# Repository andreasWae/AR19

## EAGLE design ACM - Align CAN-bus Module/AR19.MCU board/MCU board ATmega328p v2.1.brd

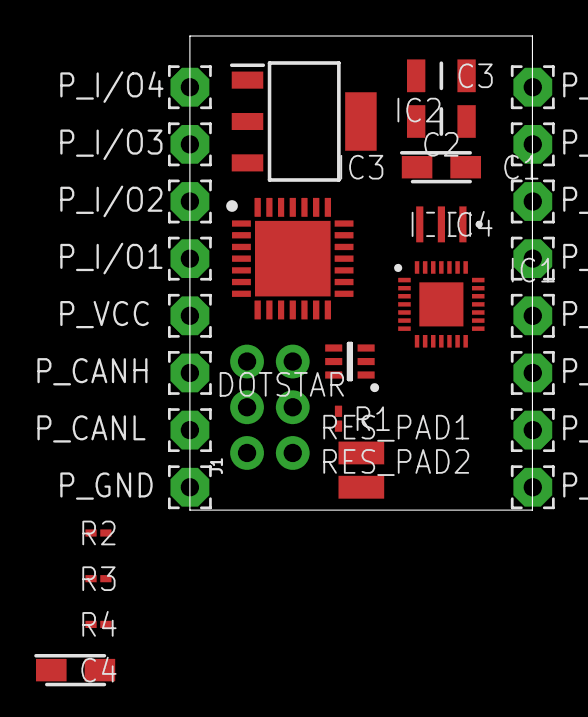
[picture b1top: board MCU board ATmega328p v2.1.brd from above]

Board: 2 copper layers, 19.0 x 26.3 mm, 32 parts (0 on the bottom side), 18 nets, no tracks yet.

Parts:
C1, C4: 10uF; CAPPM3216X180N
C2, C3: 22pF; CAPC3216X229N
DOTSTAR: COM-14608; SON75P200X200X100-6N
IC1: ATMEGA328P-MMH; QFN45P400X400X100-29N
IC2: MIC5239-5.0YS_TR; SOT230P700X170-4N
IC3: MCP25625-E_ML; QFN65P600X600X100-29N
IC4: 16Mhz; CSTCE16M0V13C99R0
J1: AVR_SPI_PROG_3X2NS; 2X3-NS
P_CANH: 2,15/1,0
P_CANL: 2,15/1,0
P_GND: 2,15/1,0
P_I/O1, P_I/O2, P_I/O3, P_I/O4, P_I/O5, P_I/O6, P_I/O7, P_I/O8, P_I/O9, P_I/O10, P_I/O11, P_I/O12: 2,15/1,0
P_VCC: 2,15/1,0
R1: 10K ohm; RESC0603X28N
R2, R3, R4: 500 ohm; RESC0603X28N
RES_PAD1, RES_PAD2: SMD1,27-2,54

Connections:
5V: C1.1, DOTSTAR.4, IC1.3, IC2.3, IC3.3, IC3.19, J1.2, R1.2
CANH: IC3.13, P_CANH.1
CANL: IC3.12, P_CANL.1
GND: C1.2, C4.1, DOTSTAR.3, IC2.2, IC3.22, IC4.2, J1.6, P_GND.1, RES_PAD2.1
MISO: IC1.14, J1.1, R2.2
MISO_MCP: IC3.28, R2.1
MOSI: IC1.13, J1.4, R3.2
MOSI_MCP: IC3.27, R3.1
unnamed: C2.1, IC4.1
unnamed: C3.1, IC4.3
OSC1: C2.2, IC1.5, IC3.21
OSC2: C3.2, IC1.6, IC3.20
RESET_MCU: IC1.25, J1.5, R1.1, RES_PAD1.1
RXCAN: IC3.5, IC3.10
SCK: IC1.15, J1.3, R4.2
SCK_MCP: IC3.26, R4.1
TXCAN: IC3.4, IC3.16
VCC: C4.2, IC2.1, P_VCC.1

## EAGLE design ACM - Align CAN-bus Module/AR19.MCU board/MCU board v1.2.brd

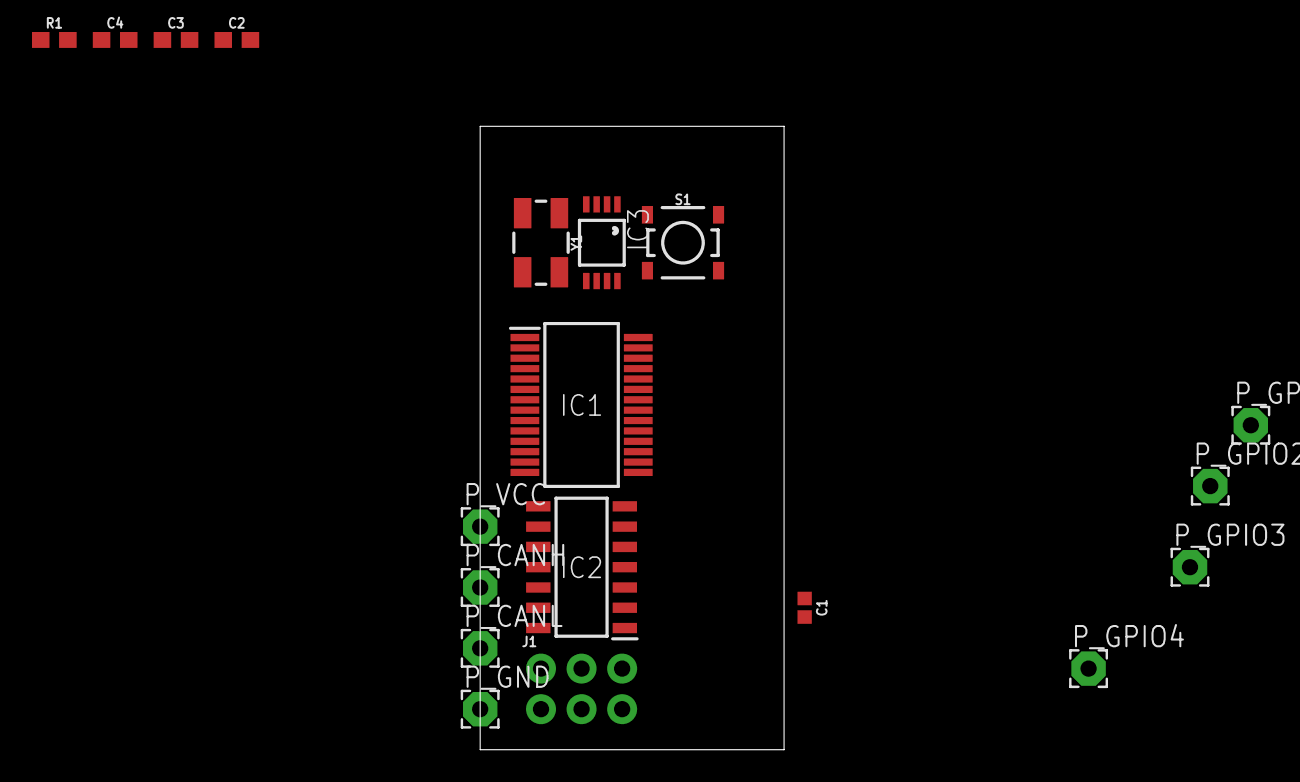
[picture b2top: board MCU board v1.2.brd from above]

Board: 2 copper layers, 19.0 x 39.0 mm, 19 parts (0 on the bottom side), 19 nets, no tracks yet.

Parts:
C1: 0.1uF; 0402
C2: 10uF; 0603
C3, C4: 22pF; 0603
IC1: MCP25625-E_SS; SOP65P780X200-28N
IC2: ATTINY84-20SSU; SOIC127P600X175-14N
IC3: LM2936MM-5.0; MINI-SO8
J1: AVR_SPI_PROG_3X2NS; 2X3-NS
P_CANH: 2,15/1,0
P_CANL: 2,15/1,0
P_GND: 2,15/1,0
P_GPIO1, P_GPIO2, P_GPIO3, P_GPIO4: 2,15/1,0
P_VCC: 2,15/1,0
R1: 10k; 0603
S1: MOMENTARY-SWITCH-SPST-SMD-4.5MM; TACTILE_SWITCH_SMD_4.5MM
Y1: 16MHz; CRYSTAL-SMD-5X3.2-4PAD

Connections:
5V: C2.1, IC1.1, IC1.19, IC1.27, IC2.1, IC3.1, J1.2, R1.2
12V: C1.1, IC3.8
CANH: IC1.4, P_CANH.1
CANL: IC1.3, P_CANL.1
CLK_CAN_OUT: IC1.22, IC2.2
CS_CAN: IC1.17, IC2.3
GND: C1.2, C2.2, C3.1, C4.1, IC1.5, IC1.10, IC1.26, IC2.14, IC3.7, J1.6, P_GND.1, S1.1, S1.4
GPIO1: IC2.13, P_GPIO1.1
GPIO2: IC2.12, P_GPIO2.1
GPIO3: IC2.11, P_GPIO3.1
GPIO4: IC2.10, P_GPIO4.1
MISO: IC1.16, IC2.8, J1.1
MOSI: IC1.15, IC2.7, J1.4
unnamed: C4.2, IC1.9, Y1.3
unnamed: C3.2, IC1.8, Y1.1
unnamed: IC1.21, IC1.28
unnamed: IC1.20, IC1.24
RESET_MCU: IC2.4, J1.5, R1.1, S1.2, S1.3
SCK: IC1.14, IC2.9, J1.3

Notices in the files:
parts and their libraries:
SparkFun-Connectors: Licensing: Creative Commons ShareAlike 4.0 International - https://creativecommons.org/licenses/by-sa/4.0
